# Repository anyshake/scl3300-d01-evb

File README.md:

# scl3300-d01-evb
🍥 SCL3300-D01 accelerometer EVB with GNSS and EEPROM for testing purpose.

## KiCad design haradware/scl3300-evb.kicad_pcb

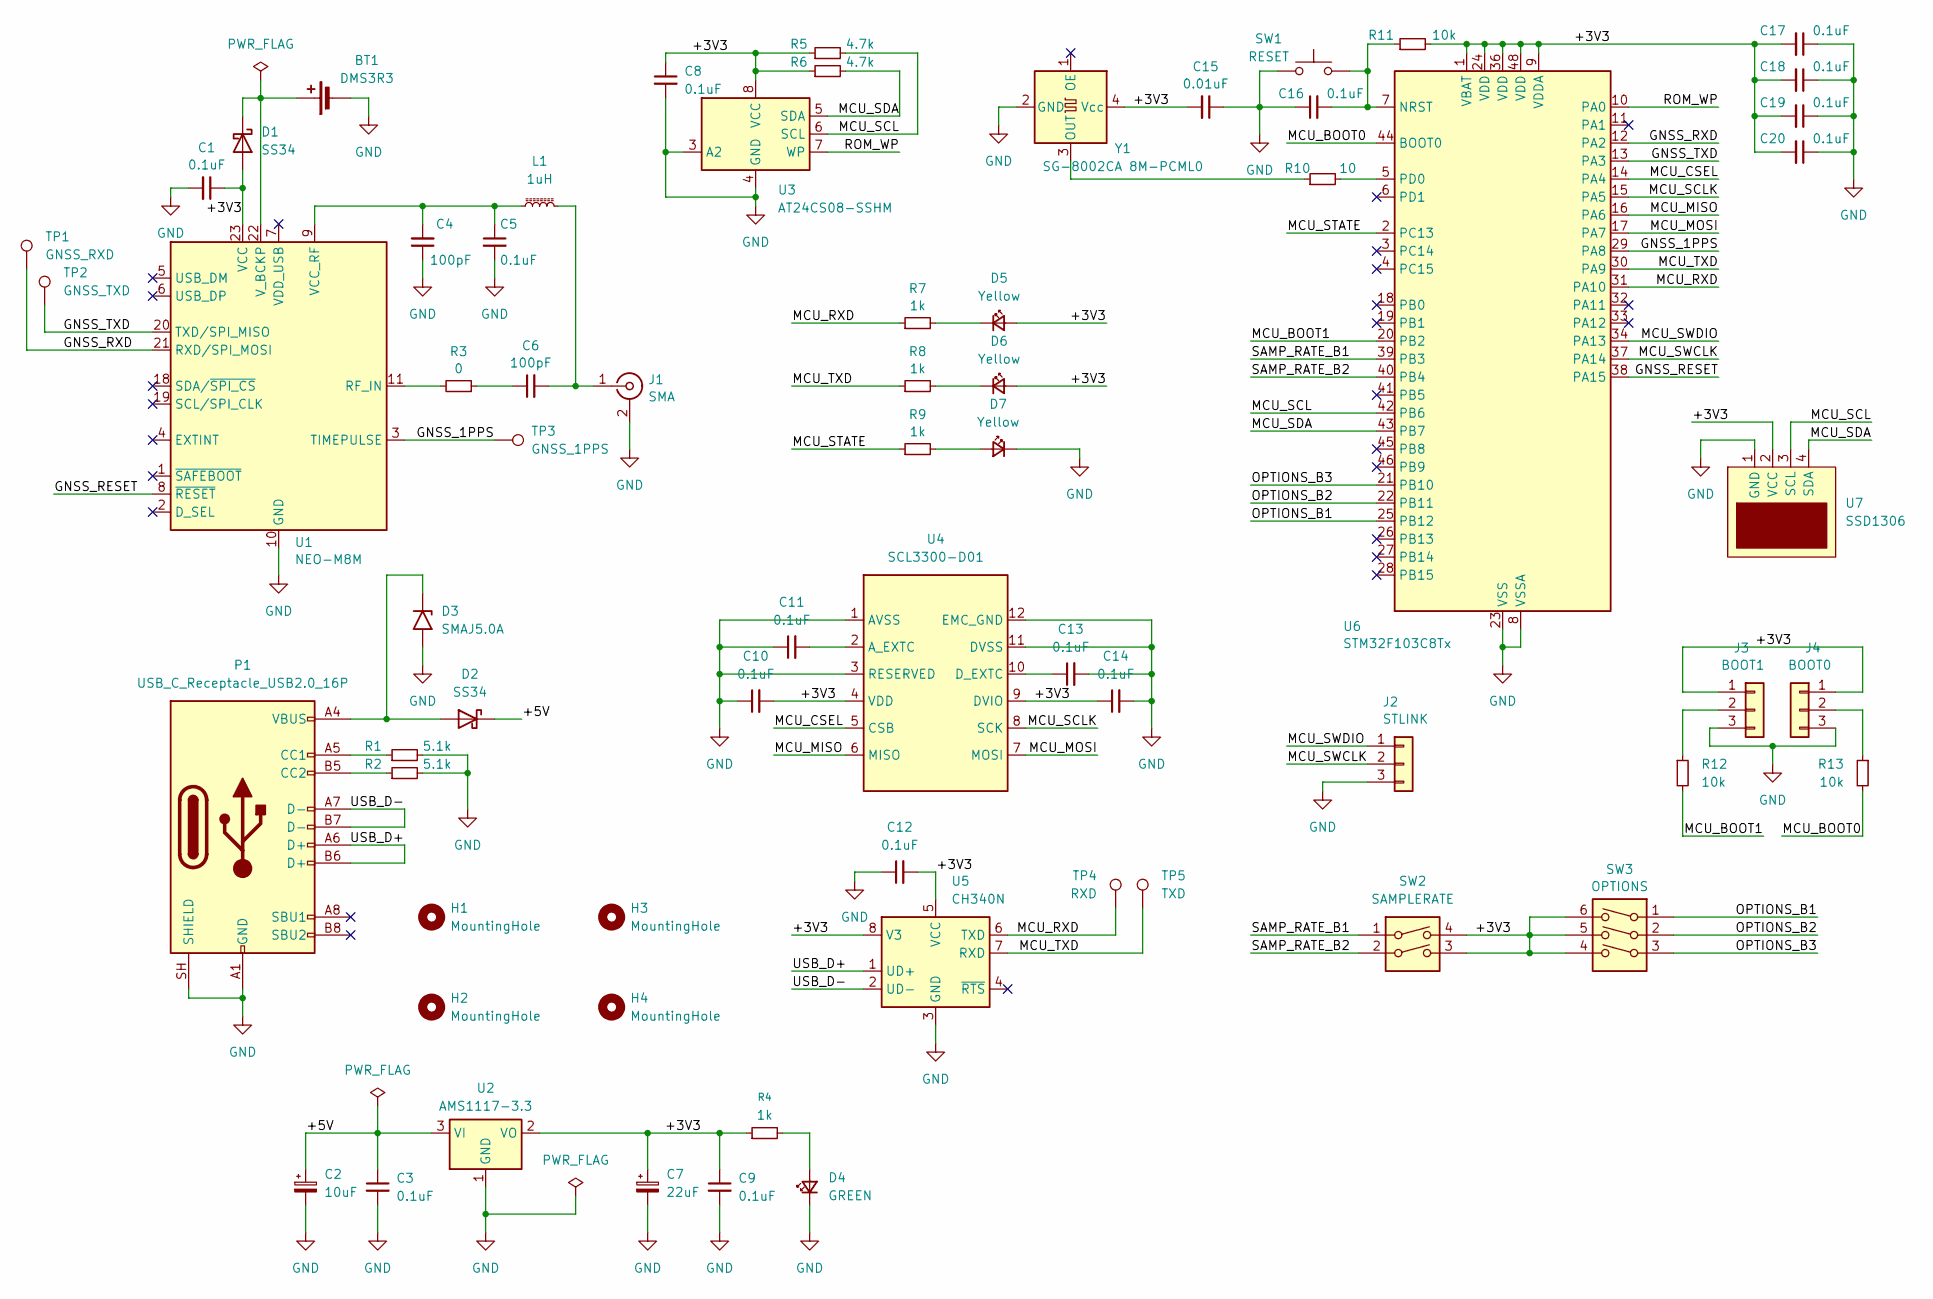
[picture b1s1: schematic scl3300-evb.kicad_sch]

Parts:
BT1: DMS3R3; BatteryHolder_Seiko_MS621F
C1, C3, C5, C8, C9, C10, C11, C12, C13, C14, C16, C17, C18, C19, C20: 0.1uF; C_0603_1608Metric
C2: 10uF; CP_EIA-3528-12_Kemet-T
C4, C6: 100pF; C_0603_1608Metric
C7: 22uF; CP_EIA-3528-12_Kemet-T
C15: 0.01uF; C_0603_1608Metric
D1, D2: SS34; D_SMA
D3: SMAJ5.0A; D_SMA
D4: GREEN; LED_0603_1608Metric
D5, D6, D7: Yellow; LED_0603_1608Metric
H1, H2, H3, H4: MountingHole; MountingHole_2.2mm_M2_DIN965_Pad
J1: SMA; SMA_Amphenol_901-144_Vertical
J2: STLINK; PinHeader_1x03_P2.54mm_Vertical
J3: BOOT1; PinHeader_1x03_P2.54mm_Vertical
J4: BOOT0; PinHeader_1x03_P2.54mm_Vertical
L1: 1uH; L_0603_1608Metric
P1: USB_C_Receptacle_USB2.0_16P; USB_C_Receptacle_HCTL_HC-TYPE-C-16P-01A
R1, R2: 5.1k; R_0603_1608Metric
R3: 0; R_0603_1608Metric
R4, R7, R8, R9: 1k; R_0603_1608Metric
R5, R6: 4.7k; R_0603_1608Metric
R10: 10; R_0603_1608Metric
R11, R12, R13: 10k; R_0603_1608Metric
SW1: RESET; SW_PUSH_6mm
SW2: SAMPLERATE; SW_DIP_SPSTx02_Slide_6.7x6.64mm_W8.61mm_P2.54mm_LowProfile
SW3: OPTIONS; SW_DIP_SPSTx03_Slide_6.7x9.18mm_W8.61mm_P2.54mm_LowProfile
TP1: GNSS_RXD; TestPoint_Pad_D1.0mm
TP2: GNSS_TXD; TestPoint_Pad_D1.0mm
TP3: GNSS_1PPS; TestPoint_Pad_D1.0mm
TP4: RXD; TestPoint_Pad_D1.0mm
TP5: TXD; TestPoint_Pad_D1.0mm
U1: NEO-M8M; ublox_NEO
U2: AMS1117-3.3; SOT-223-3_TabPin2
U3: AT24CS08-SSHM; SOIC-8_3.9x4.9mm_P1.27mm
U4: SCL3300-D01; DFL-12_L8.6-W7.0-P1.00-LS7.6-BL
U5: CH340N; JEITA_SOIC-8_3.9x4.9mm_P1.27mm
U6: STM32F103C8Tx; LQFP-48_7x7mm_P0.5mm
U7: SSD1306
Y1: SG-8002CA 8M-PCML0; Oscillator_SMD_SeikoEpson_SG8002CA-4Pin_7.0x5.0mm

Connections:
/+3V3: C1.1, C7.1, C8.1, C9.1, C10.2, C12.2, C14.1, C15.2, C17.2, C18.2, C19.2, C20.2, D1.2 (A), D5.2 (A), D6.2 (A), J3.1, J4.1, R4.1, R5.1, R6.1, R11.2, SW2.3, SW2.4, SW3.4, SW3.5, SW3.6, U1.23 (VCC), U2.2 (VO), U3.8 (VCC), U4.4 (VDD), U4.9 (DVIO), U5.5 (VCC), U5.8 (V3), U6.1 (VBAT), U6.9 (VDDA), U6.24 (VDD), U6.36 (VDD), U6.48 (VDD), U7.2 (VCC), Y1.4 (Vcc)
/+5V: C2.1, C3.1, D2.1 (K), U2.3 (VI)
/GNSS_1PPS: TP3.1 (1_1), U1.3 (TIMEPULSE), U6.29 (PA8)
/GNSS_RESET: U1.8 (~RESET), U6.38 (PA15)
/GNSS_RXD: TP1.1 (1_1), U1.21 (RXD/SPI_MOSI), U6.12 (PA2)
/GNSS_TXD: TP2.1 (1_1), U1.20 (TXD/SPI_MISO), U6.13 (PA3)
/MCU_BOOT0: R13.2, U6.44 (BOOT0)
/MCU_BOOT1: R12.2, U6.20 (PB2)
/MCU_CSEL: U4.5 (CSB), U6.14 (PA4)
/MCU_MISO: U4.6 (MISO), U6.16 (PA6)
/MCU_MOSI: U4.7 (MOSI), U6.17 (PA7)
/MCU_RXD: R7.1, TP4.1 (1_1), U5.6 (TXD), U6.31 (PA10)
/MCU_SCL: R5.2, U3.6 (SCL), U6.42 (PB6), U7.3 (SCL)
/MCU_SCLK: U4.8 (SCK), U6.15 (PA5)
/MCU_SDA: R6.2, U3.5 (SDA), U6.43 (PB7), U7.4 (SDA)
/MCU_STATE: R9.1, U6.2 (PC13)
/MCU_SWCLK: J2.2, U6.37 (PA14)
/MCU_SWDIO: J2.1, U6.34 (PA13)
/MCU_TXD: R8.1, TP5.1 (1_1), U5.7 (RXD), U6.30 (PA9)
/OPTIONS_B1: SW3.1, U6.25 (PB12)
/OPTIONS_B2: SW3.2, U6.22 (PB11)
/OPTIONS_B3: SW3.3, U6.21 (PB10)
/ROM_WP: U3.7 (WP), U6.10 (PA0)
/SAMP_RATE_B1: SW2.1, U6.39 (PB3)
/SAMP_RATE_B2: SW2.2, U6.40 (PB4)
/USB_D+: P1.A6 (D+), P1.B6 (D+), U5.1 (UD+)
/USB_D-: P1.A7 (D-), P1.B7 (D-), U5.2 (UD-)
GND: BT1.2 (-), C1.2, C2.2, C3.2, C4.1, C5.2, C7.2, C8.2, C9.2, C10.1, C11.1, C12.1, C13.2, C14.2, C15.1, C16.1, C17.1, C18.1, C19.1, C20.1, D3.2 (A2), D4.1 (K), D7.1 (K), J1.2 (Ext), J2.3, J3.3, J4.3, P1.A1 (GND), P1.A12 (GND), P1.B1 (GND), P1.B12 (GND), P1.SH (SHIELD), R1.2, R2.2, SW1.1, U1.10 (GND), U1.12 (GND), U1.13 (GND), U1.24 (GND), U2.1 (GND), U3.3 (A2), U3.4 (GND), U4.1 (AVSS), U4.3 (RESERVED), U4.11 (DVSS), U4.12 (EMC_GND), U5.3 (GND), U6.8 (VSSA), U6.23 (VSS), U6.35 (VSS), U6.47 (VSS), U7.1 (GND), Y1.2 (GND)
unnamed: BT1.1 (+), D1.1 (K), U1.22 (V_BCKP)
unnamed: C6.1, R3.1
unnamed: D2.2 (A), D3.1 (A1), P1.A4 (VBUS), P1.A9 (VBUS), P1.B4 (VBUS), P1.B9 (VBUS)
unnamed: D4.2 (A), R4.2
unnamed: D5.1 (K), R7.2
unnamed: D6.1 (K), R8.2
unnamed: D7.2 (A), R9.2
unnamed: C6.2, J1.1 (In), L1.2
unnamed: J3.2, R12.1
unnamed: J4.2, R13.1
unnamed: P1.A5 (CC1), R1.1
unnamed: P1.B5 (CC2), R2.1
unnamed: R3.2, U1.11 (RF_IN)
unnamed: C4.2, C5.1, L1.1, U1.9 (VCC_RF)
unnamed: C11.2, U4.2 (A_EXTC)
unnamed: C13.1, U4.10 (D_EXTC)
unnamed: C16.2, R11.1, SW1.2, U6.7 (NRST)
unnamed: R10.2, U6.5 (PD0)
unnamed: R10.1, Y1.3 (OUT)

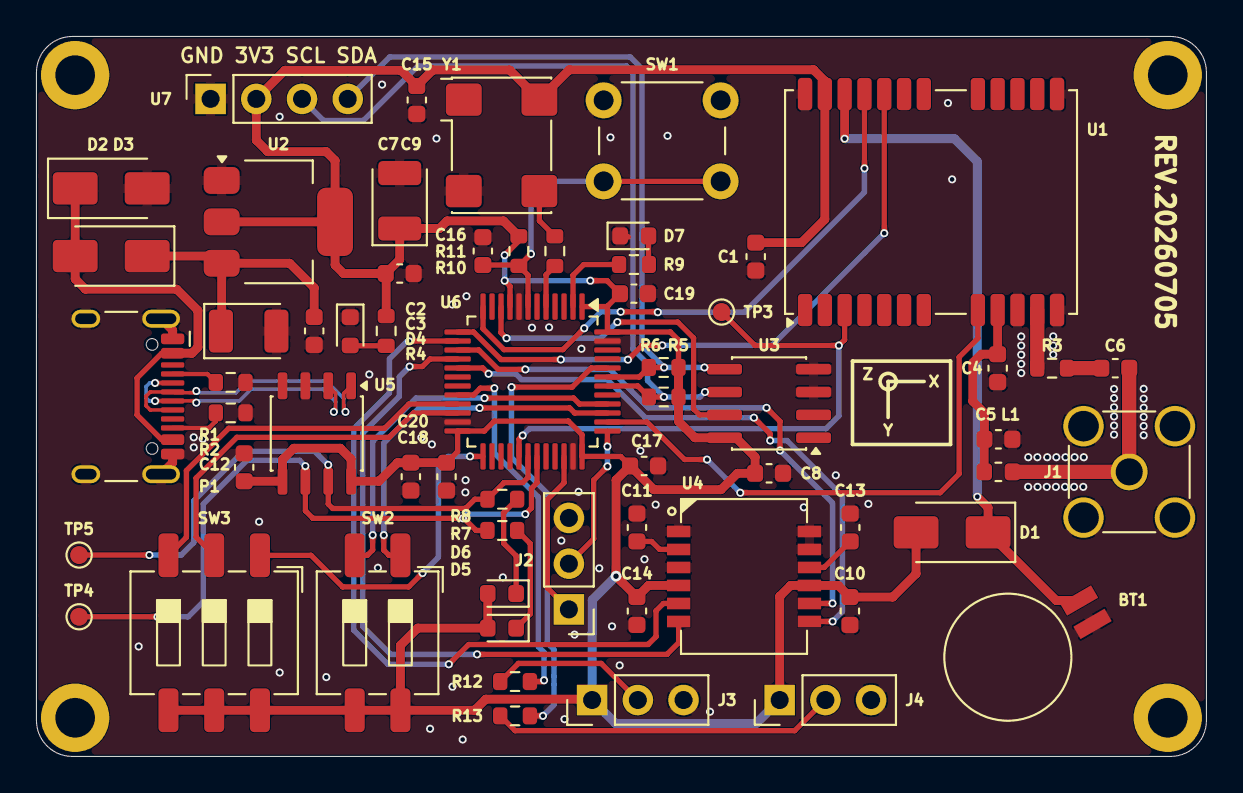
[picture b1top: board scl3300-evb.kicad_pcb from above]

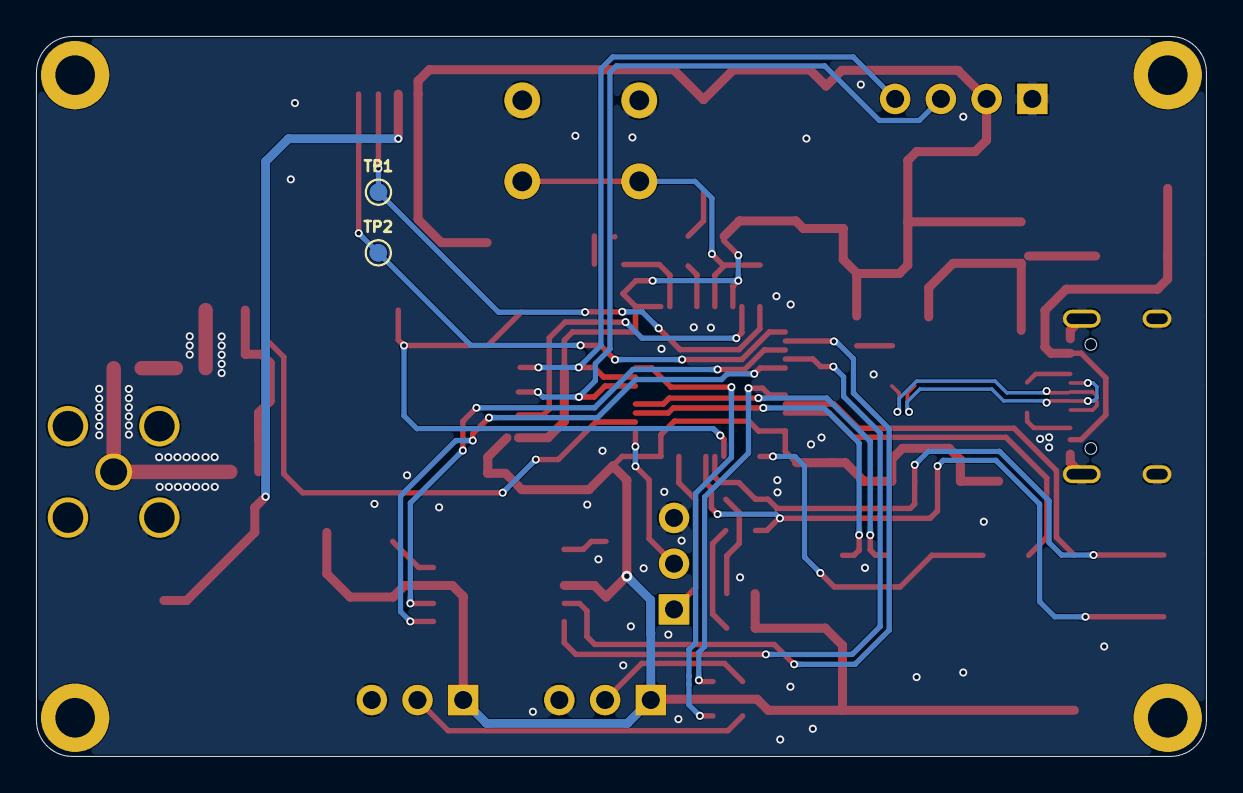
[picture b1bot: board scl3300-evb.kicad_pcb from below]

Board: 2 copper layers, 65.0 x 40.0 mm, 67 parts (2 on the bottom side), 47 nets.

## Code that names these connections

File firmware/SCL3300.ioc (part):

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Mcu.Name=STM32F103C(8-B)Tx
Mcu.Package=LQFP48
Mcu.UserName=STM32F103C8Tx
PA10.Mode=Asynchronous
PA10.Signal=USART1_RX
PA13.Mode=Serial_Wire
PA13.Signal=SYS_JTMS-SWDIO
PA14.Mode=Serial_Wire
PA14.Signal=SYS_JTCK-SWCLK
PA2.Mode=Asynchronous
PA2.Signal=USART2_TX
PA3.Mode=Asynchronous
PA3.Signal=USART2_RX
PA5.Mode=Full_Duplex_Master
PA5.Signal=SPI1_SCK
PA6.Mode=Full_Duplex_Master
PA6.Signal=SPI1_MISO
PA7.Mode=Full_Duplex_Master
PA7.Signal=SPI1_MOSI
PA8.Signal=GPXTI8
PA9.Mode=Asynchronous
PA9.Signal=USART1_TX
PB6.Mode=I2C
PB6.Signal=I2C1_SCL
PB7.Mode=I2C
PB7.Signal=I2C1_SDA
PC13-TAMPER-RTC.Signal=GPIO_Output
PD0-OSC_IN.Mode=HSE-External-Clock-Source
PD0-OSC_IN.Signal=RCC_OSC_IN
PD1-OSC_OUT.Mode=HSE-External-Clock-Source
PD1-OSC_OUT.Signal=RCC_OSC_OUT
RCC.HSE_Timout=0xffffffff
RCC.SYSCLKFreq_VALUE=72000000
RCC.SYSCLKSource=RCC_SYSCLKSOURCE_PLLCLK
board=custom

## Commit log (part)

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2026-04-19 chore: rename PCB folder
2026-04-19 chore: repository init
2026-04-19 chore: move test tool to root
